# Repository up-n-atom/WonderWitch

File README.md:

# WonderWitch Reproduction

## Schematic Capture

- [x] Create symbols
- [x] Block design

[schematic.pdf](/Schematic.pdf)

## PCB Layout

- [x] Create footprints
- [x] Route top layer 
- [x] Route bottom layer
- [x] Plane top layer
- [x] Plane bottom layer
- [x] Teardrop top layer
- [x] Teardrop bottom layer
- [ ] Silkscreen top layer

## Manufacturing Notes

- Do not plate slots and non-plated through-holes, ask fabricator to adjust keep-away. The original design was intended for electroplating and not electroless.
- Do not submit the incomplete silkscreen gerbers.

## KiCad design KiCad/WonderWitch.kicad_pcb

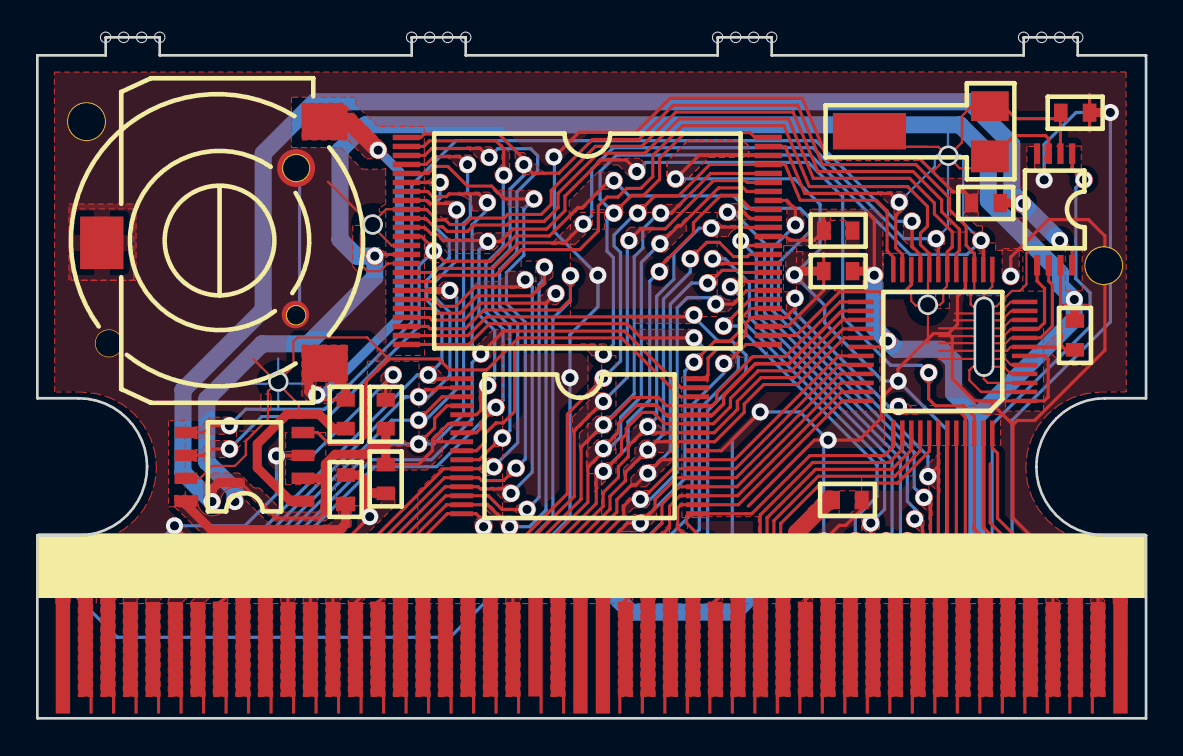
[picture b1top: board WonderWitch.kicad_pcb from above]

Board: 2 copper layers, 61.6 x 37.8 mm, 18 parts (0 on the bottom side), 64 nets.

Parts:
BT1: CR1616; BTHLDR
C1, C3, C4, C7, C8: 10nF; 0603
C2, C5: 1uF; 0603
C6: 3pF; 0603
J1: WSCE; EDGE
R1, R2: R103; 0603
U1: MBM29DL400TC; TSOP-I-48
U2: GIZA; SOP-8
U3: BANDAI2003; LQFP-48
U4: UPD442000A; STSOP-32
U5: S3511A; SSOP-8
Y1: CMR200T; WX2

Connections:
/A0: J1.26, U3.34, U4.20
/A1-0: J1.27, U1.25, U3.35, U4.19
/A2-1: J1.28, U1.24, U3.36, U4.18
/A3-2: J1.29, U1.23, U3.37, U4.17
/A4-3: J1.13, U1.22, U4.16
/A5-4: J1.12, U1.21, U4.15
/A6-5: J1.11, U1.20, U4.14
/A7-6: J1.10, U1.19, U4.13
/A8-7: J1.6, U1.18, U4.3
/A9-8: J1.5, U1.8, U4.2
/A10-9: J1.3, U1.7, U4.31
/A11-10: J1.4, U1.6, U4.1
/A12-11: J1.9, U1.5, U4.12
/A13-12: J1.7, U1.4, U4.4
/A14-13: J1.8, U1.3, U4.11
/A15-14: J1.2, U1.2, U4.7
/A16: J1.33, U3.41
/A16-15: U1.1, U3.15, U4.10
/A17: J1.32, U3.40
/A17-16: U1.48, U3.14, U4.9
/A18: J1.31, U3.39
/A18-17: U1.17, U3.20
/A19: J1.30, U3.38
/A19-18: U1.16, U3.19
/A20-19: U1.9, U3.17
/A21-20: U1.10, U3.18
/CE: J1.45, U3.47
/CLK: J1.47, U3.48
/NOR_BYTE: U1.47, U3.23
/NOR_CE: U1.26, U3.22
/OE: J1.43, U1.28, U3.45, U4.32
/Q0: J1.23, U1.29, U3.33, U4.21
/Q1: J1.22, U1.31, U3.32, U4.22
/Q2: J1.21, U1.33, U3.31, U4.23
/Q3: J1.20, U1.35, U3.29, U4.25
/Q4: J1.19, U1.38, U3.28, U4.26
/Q5: J1.18, U1.40, U3.27, U4.27
/Q6: J1.17, U1.42, U3.26, U4.28
/Q7: J1.16, U1.44, U3.25, U4.29
/Q8: J1.34, U1.30
/Q9: J1.35, U1.32
/Q10: J1.36, U1.34
/Q11: J1.37, U1.36
/Q12: J1.38, U1.39
/Q13: J1.39, U1.41
/Q14: J1.15, U1.43
/Q15: J1.14, U1.45, U3.24
/RST: J1.40, U1.12, U3.42
/RTC_CK: U3.8, U5.6
/RTC_CS: U3.9, U5.5
/RTC_INT: J1.46, U5.1
/RTC_IO: R2.1, U3.7, U5.7
/SO: J1.41, U3.43
/SRAM_CE: U2.4, U4.30
/SS: J1.42, U3.44
/SUP_CS: U2.5, U3.21
/WE: J1.44, U1.11, U3.46, U4.5
unnamed: BT1.1, R1.1
unnamed: C6.1, U5.2, Y1.1
unnamed: R1.2, U2.1
unnamed: U5.3, Y1.2
VDD: C1.1, C4.1, C5.1, C8.1, J1.24, J1.25, R2.2, U1.14, U1.37, U2.8, U3.30
VMEM: C2.1, C3.1, C7.1, U2.2, U4.8, U5.8
VSS: BT1.2, BT1.VSS, C1.2, C2.2, C3.2, C4.2, C5.2, C6.2, C7.2, C8.2, J1.1, J1.48, J1.VSS, U1.27, U1.46, U2.3, U3.1, U3.6, U3.16, U4.24, U5.4

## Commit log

2021-05-07 Add project files
2021-05-07 Add images
2021-05-07 Add schematic output
2021-10-05 Update README.md
    Add to-do list and manufacturing notes.
